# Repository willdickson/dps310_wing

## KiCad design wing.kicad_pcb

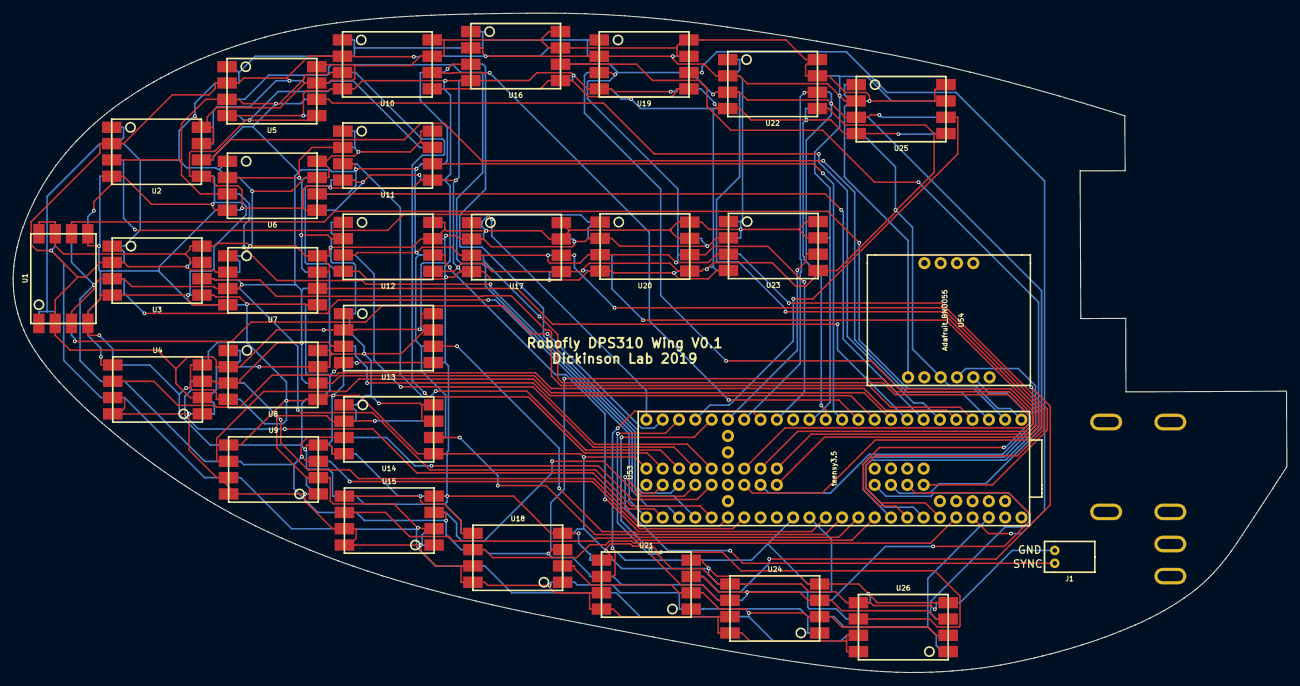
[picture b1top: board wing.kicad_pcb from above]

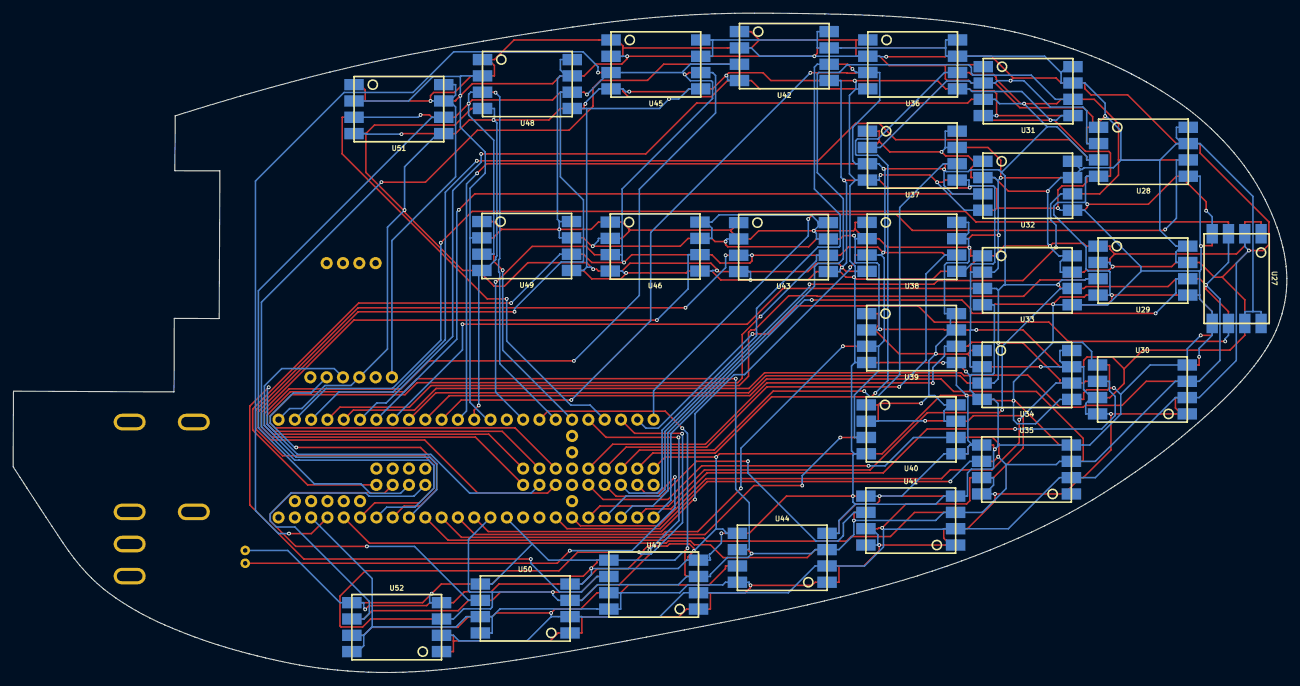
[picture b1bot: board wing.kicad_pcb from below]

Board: 2 copper layers, 198.4 x 102.7 mm, 61 parts (26 on the bottom side), 60 nets.

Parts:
H1, H2, H3, H4, H5, H6: cable_tie_hole
J1: pin_array_2x1; JST_PH_2PIN
U1, U2: DSP310_DEV; DPS310_DEV
U3, U4, U5, U6, U7, U8, U9, U10, U11, U12, U13, U14, U15, U16, U17, U18, U19, U20, U21, U22, U23, U24, U25, U26, U27, U28, U29, U30, U31, U32, U33, U34, U35, U36, U37, U38, U39, U40, U41, U42, U43, U44, U45, U46, U47, U48, U49, U50, U51, U52: DPS310_DEV
U53: teensy3.5
U54: Adafruit_BNO055

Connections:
/3V3: U1.7, U1.8, U2.7, U2.8, U3.7, U3.8, U4.7, U4.8, U5.7, U5.8, U6.7, U6.8, U7.7, U7.8, U8.7, U8.8, U9.7, U9.8, U10.7, U10.8, U11.7, U11.8, U12.7, U12.8, U13.7, U13.8, U14.7, U14.8, U15.7, U15.8, U16.7, U16.8, U17.7, U17.8, U18.7, U18.8, U19.7, U19.8, U20.7, U20.8, U21.7, U21.8, U22.7, U22.8, U23.7, U23.8, U24.7, U24.8, U25.7, U25.8, U26.7, U26.8, U27.7, U27.8, U28.7, U28.8, U29.7, U29.8, U30.7, U30.8, U31.7, U31.8, U32.7, U32.8, U33.7, U33.8, U34.7, U34.8, U35.7, U35.8, U36.7, U36.8, U37.7, U37.8, U38.7, U38.8, U39.7, U39.8, U40.7, U40.8, U41.7, U41.8, U42.7, U42.8, U43.7, U43.8, U44.7, U44.8, U45.7, U45.8, U46.7, U46.8, U47.7, U47.8, U48.7, U48.8, U49.7, U49.8, U50.7, U50.8, U51.7, U51.8, U52.7, U52.8, U53.46, U54.1
/DPS_CS00: U1.6, U53.2
/DPS_CS01: U2.6, U53.3
/DPS_CS02: U3.6, U53.4
/DPS_CS03: U4.6, U53.5
/DPS_CS04: U5.6, U53.6
/DPS_CS05: U6.6, U53.7
/DPS_CS06: U7.6, U53.8
/DPS_CS07: U8.6, U53.9
/DPS_CS08: U9.6, U53.10
/DPS_CS09: U10.6, U53.11
/DPS_CS10: U11.6, U53.12
/DPS_CS11: U12.6, U53.36
/DPS_CS12: U13.6, U53.37
/DPS_CS13: U14.6, U53.38
/DPS_CS14: U15.6, U53.39
/DPS_CS15: U16.6, U53.42
/DPS_CS16: U17.6, U53.43
/DPS_CS17: U18.6, U53.44
/DPS_CS18: U19.6, U53.45
/DPS_CS19: U20.6, U53.16
/DPS_CS20: U21.6, U53.17
/DPS_CS21: U22.6, U53.18
/DPS_CS22: U23.6, U53.19
/DPS_CS23: U24.6, U53.20
/DPS_CS24: U25.6, U53.21
/DPS_CS25: U26.6, U53.22
/DPS_CS26: U27.6, U53.23
/DPS_CS27: U28.6, U53.24
/DPS_CS28: U29.6, U53.25
/DPS_CS29: U30.6, U53.26
/DPS_CS30: U31.6, U53.27
/DPS_CS31: U32.6, U53.28
/DPS_CS32: U33.6, U53.29
/DPS_CS33: U34.6, U53.30
/DPS_CS34: U35.6, U53.31
/DPS_CS35: U36.6, U53.50
/DPS_CS36: U37.6, U53.51
/DPS_CS37: U38.6, U53.52
/DPS_CS38: U39.6, U53.53
/DPS_CS39: U40.6, U53.54
/DPS_CS40: U41.6, U53.55
/DPS_CS41: U42.6, U53.56
/DPS_CS42: U43.6, U53.59
/DPS_CS43: U44.6, U53.60
/DPS_CS44: U45.6, U53.61
/DPS_CS45: U46.6, U53.62
/DPS_CS46: U47.6, U53.63
/DPS_CS47: U48.6, U53.64
/DPS_CS48: U49.6, U53.69
/DPS_CS49: U50.6, U53.70
/DPS_CS50: U51.6, U53.71
/DPS_CS51: U52.6, U53.72
/MISO: U1.2, U2.2, U3.2, U4.2, U5.2, U6.2, U7.2, U8.2, U9.2, U10.2, U11.2, U12.2, U13.2, U14.2, U15.2, U16.2, U17.2, U18.2, U19.2, U20.2, U21.2, U22.2, U23.2, U24.2, U25.2, U26.2, U27.2, U28.2, U29.2, U30.2, U31.2, U32.2, U33.2, U34.2, U35.2, U36.2, U37.2, U38.2, U39.2, U40.2, U41.2, U42.2, U43.2, U44.2, U45.2, U46.2, U47.2, U48.2, U49.2, U50.2, U51.2, U52.2, U53.14
/MOSI: U1.4, U2.4, U3.4, U4.4, U5.4, U6.4, U7.4, U8.4, U9.4, U10.4, U11.4, U12.4, U13.4, U14.4, U15.4, U16.4, U17.4, U18.4, U19.4, U20.4, U21.4, U22.4, U23.4, U24.4, U25.4, U26.4, U27.4, U28.4, U29.4, U30.4, U31.4, U32.4, U33.4, U34.4, U35.4, U36.4, U37.4, U38.4, U39.4, U40.4, U41.4, U42.4, U43.4, U44.4, U45.4, U46.4, U47.4, U48.4, U49.4, U50.4, U51.4, U52.4, U53.13
/SCK: U1.3, U2.3, U3.3, U4.3, U5.3, U6.3, U7.3, U8.3, U9.3, U10.3, U11.3, U12.3, U13.3, U14.3, U15.3, U16.3, U17.3, U18.3, U19.3, U20.3, U21.3, U22.3, U23.3, U24.3, U25.3, U26.3, U27.3, U28.3, U29.3, U30.3, U31.3, U32.3, U33.3, U34.3, U35.3, U36.3, U37.3, U38.3, U39.3, U40.3, U41.3, U42.3, U43.3, U44.3, U45.3, U46.3, U47.3, U48.3, U49.3, U50.3, U51.3, U52.3, U53.35
/SCL: U53.41, U54.5
/SDA: U53.40, U54.4
/SYNC: J1.2, U53.57
GND: J1.1, U1.5, U2.5, U3.5, U4.5, U5.5, U6.5, U7.5, U8.5, U9.5, U10.5, U11.5, U12.5, U13.5, U14.5, U15.5, U16.5, U17.5, U18.5, U19.5, U20.5, U21.5, U22.5, U23.5, U24.5, U25.5, U26.5, U27.5, U28.5, U29.5, U30.5, U31.5, U32.5, U33.5, U34.5, U35.5, U36.5, U37.5, U38.5, U39.5, U40.5, U41.5, U42.5, U43.5, U44.5, U45.5, U46.5, U47.5, U48.5, U49.5, U50.5, U51.5, U52.5, U53.1, U53.34, U53.49, U54.3

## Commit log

2019-06-27 Project creation.
2019-06-28 Finished initial schematic, footprint design and footprint assignment.
2019-06-29 Finished initial design. Needs to be routed.
2020-04-13 Added readme and images.
2020-04-13 Fixed issue with README.
